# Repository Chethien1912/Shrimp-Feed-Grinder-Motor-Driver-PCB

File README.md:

# Shrimp-Feed-Grinder-Motor-Driver-PCB
Board dùng vi điều khiển STM32F0 làm trung tâm điều khiển.

STM32 xử lý các tín hiệu vào/ra, điều khiển PWM, relay, MOSFET công suất và LED 7 đoạn.

Phần driver sử dụng MOSFET công suất IRF540N để điều khiển thắng điện từ DC.

Tín hiệu điều khiển MOSFET được cách ly bằng opto PC817, giúp bảo vệ vi điều khiển khỏi nhiễu và xung áp từ tải công suất.

Mạch có diode và zener bảo vệ MOSFET khi đóng/ngắt cuộn thắng điện từ.

Board điều khiển động cơ 220VAC công suất 0.5HP thông qua relay và mạch công suất.

Khối relay dùng để điều khiển các trạng thái chạy, dừng, thắng và chuyển mạch động cơ.

Mạch khởi động mềm sử dụng nguyên lý TRIAC - DIAC, giúp giảm dòng khởi động ban đầu cho động cơ.

Điều khiển tốc độ hoặc mức công suất bằng tín hiệu PWM từ vi điều khiển.

Hiển thị trạng thái hoạt động bằng LED 7 đoạn 4 digit.

LED 7 đoạn được điều khiển qua IC TM1637, chỉ cần hai chân giao tiếp CLK và DIO.

Khối nguồn tạo các mức điện áp cần thiết như 12V, 3.3V và 55VDC.

Nguồn 3.3V cấp cho STM32 và IC hiển thị.

Nguồn 12V cấp cho relay và mạch điều khiển phụ.

Nguồn 55VDC dùng cho phần thắng điện từ.

Tổng thể board tập trung vào điều khiển phần cứng cho động cơ, gồm điều khiển PWM, thắng điện từ, khởi động mềm và hiển thị trạng thái.

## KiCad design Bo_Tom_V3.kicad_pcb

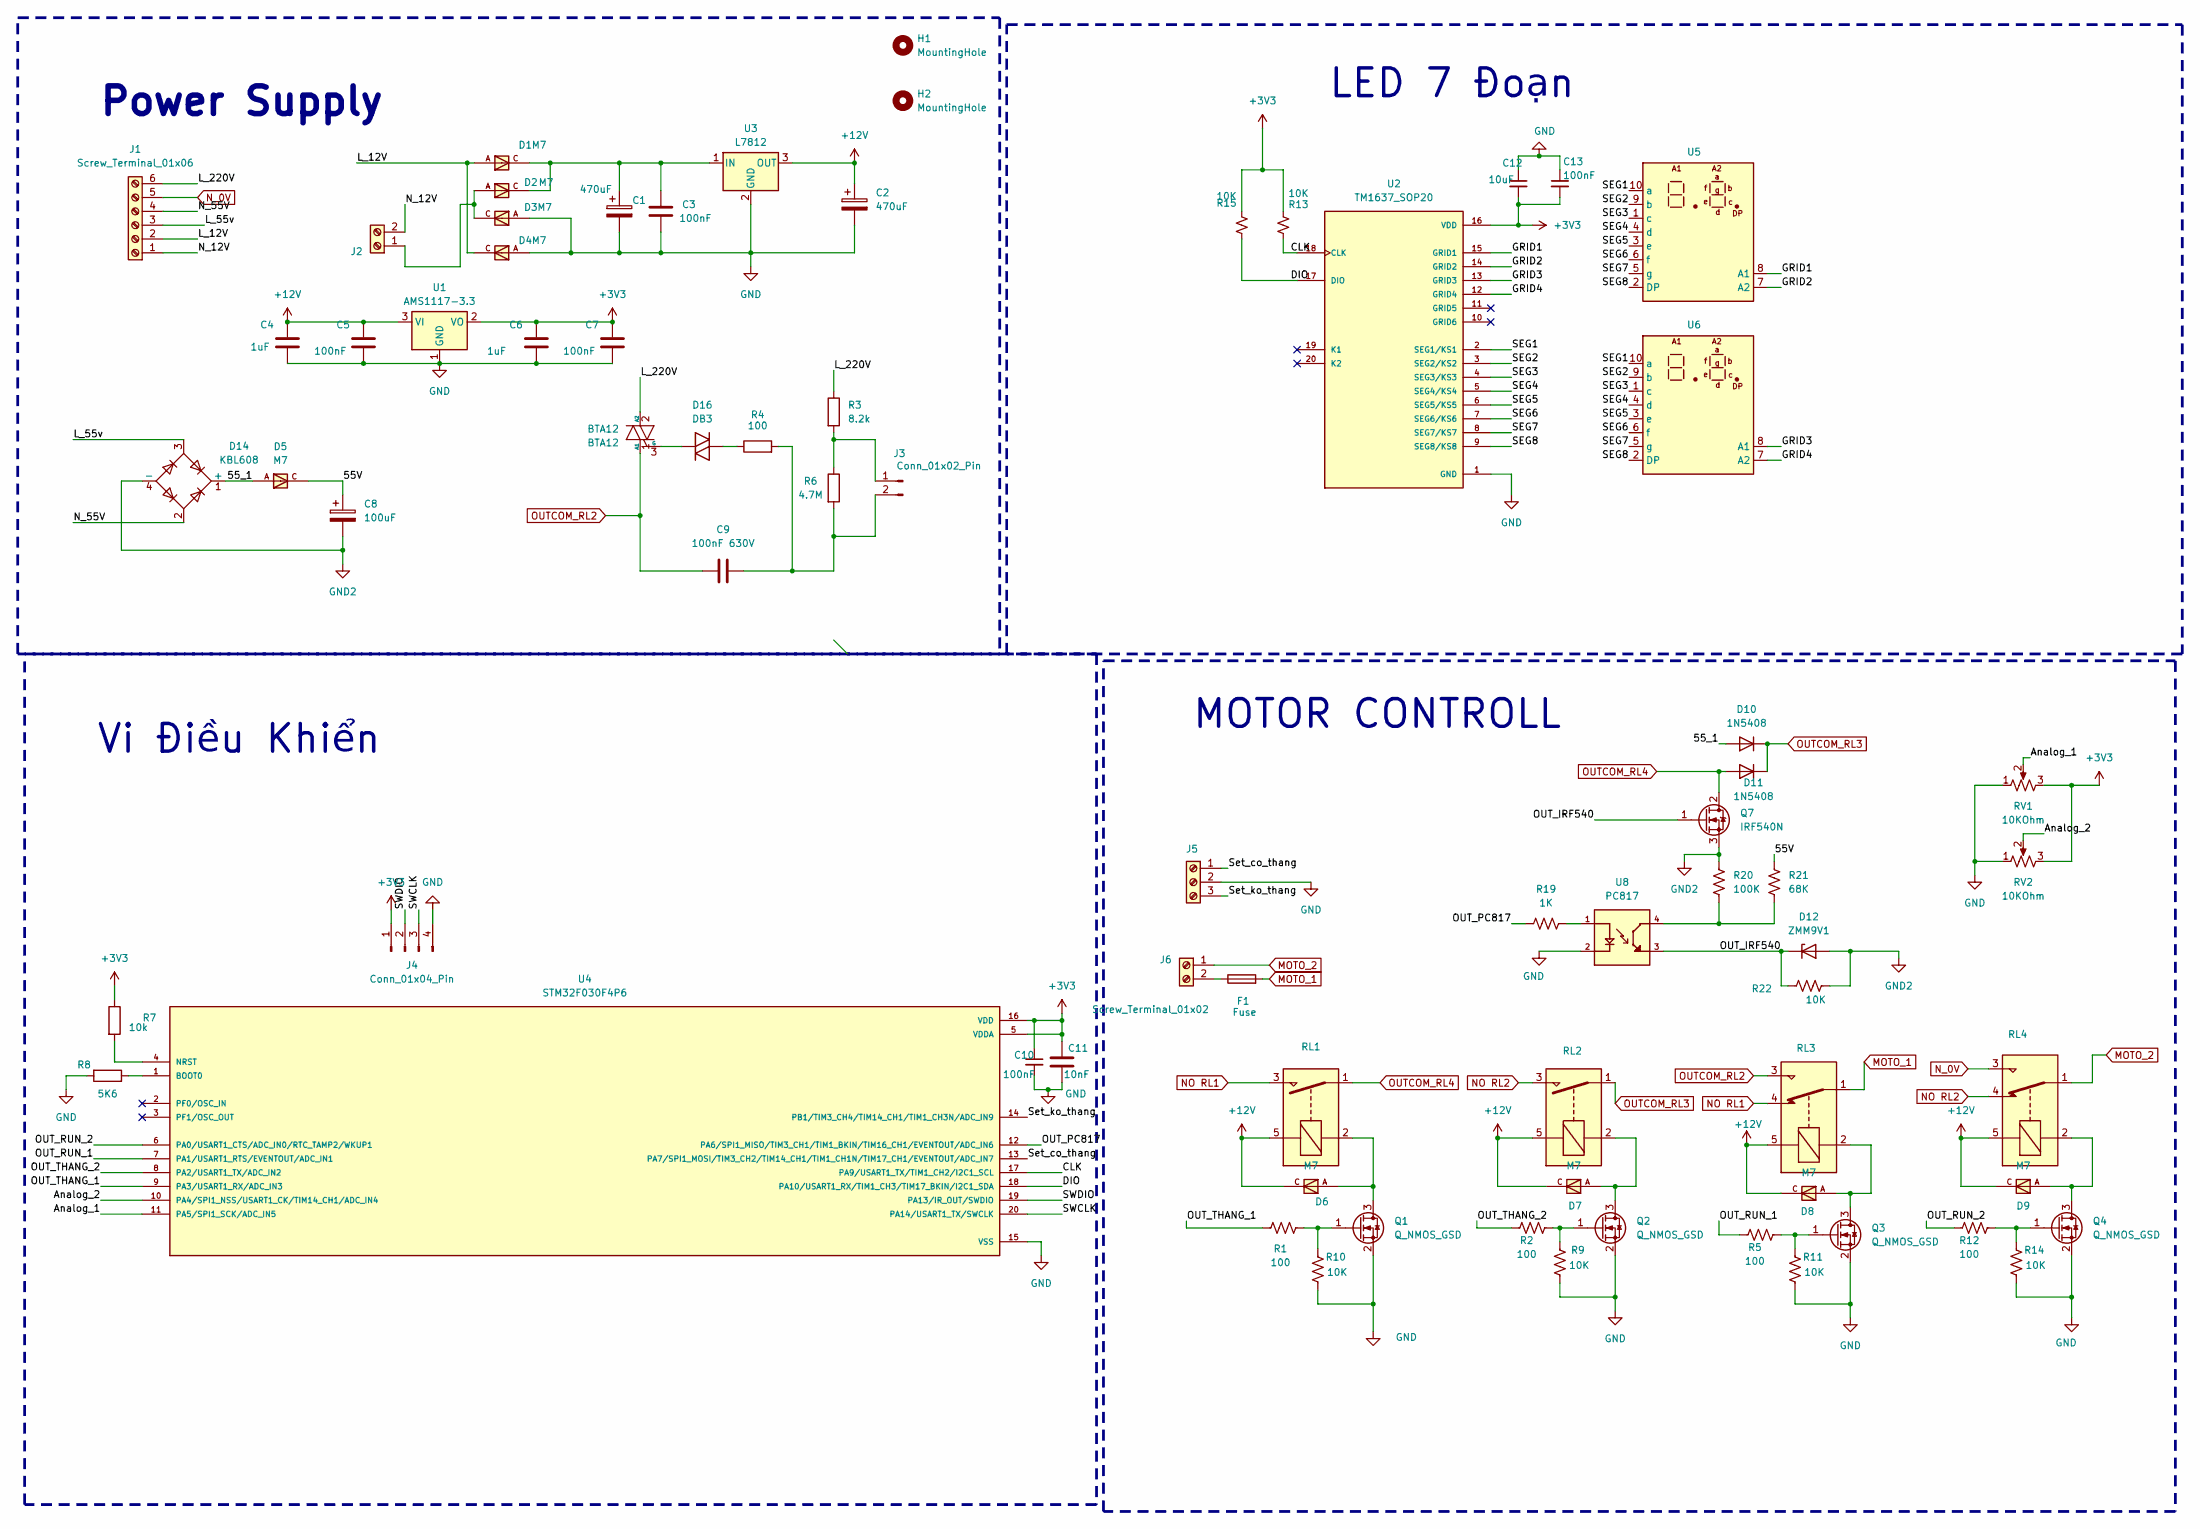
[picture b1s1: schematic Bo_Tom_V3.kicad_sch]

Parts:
BTA12: BTA12; TO-220-3_Vertical
C1, C2: 470uF; C_Radial_D8.0mm_H11.5mm_P3.50mm
C3, C5, C7, C13: 100nF; C_0603_1608Metric
C4, C6: 1uF; C_0603_1608Metric
C8: 100uF; C_Radial_D10.0mm_H16.0mm_P5.00mm
C9: 100nF 630V; C_Rect_L11.5mm_W4.5mm_P10.00mm_MKT
C10: 100nF; C_0603
C11: 10nF; C_0603_1608Metric
C12: 10uF; C_0603_1608Metric
D1, D2, D3, D4, D5, D6, D7, D8, D9: M7; DIOM505270X240; MPN M7
D10, D11: 1N5408; D_DO-201AD_P15.24mm_Horizontal
D12: ZMM9V1; diode_ZMM
D14: KBL608; KLB608
D16: DB3; D_DO-35_SOD27_P7.62mm_Horizontal
F1: Fuse; Fuse_Bourns_MF-RG300
H1, H2: MountingHole; Hole_3mm
J1: Screw_Terminal_01x06; TE_826576-6_1x06_P3.96mm_Vertical
J2, J6: Screw_Terminal_01x02; TE_826576-2_1x02_P3.96mm_Vertical
J3: Conn_01x02_Pin; Conn-Vert-THT-2P-2.54mm-S2B_XH_SM4_TB
J4: Conn_01x04_Pin; PinHeader_1x04_P2.54mm_Vertical
J5: Screw_Terminal_01x03; Conn-Vert-THT-3P-2.54mm-S3B_XH_SM4_TB
Q1, Q2, Q3, Q4: Q_NMOS_GSD; SOT-23
Q7: IRF540N; TO-220-3_Vertical
R1, R2, R5, R12: 100; R_0603_1608Metric
R3: 8.2k; R_0603
R4: 100; R_0603
R6: 4.7M; R_0805
R7: 10k; R_0603_1608Metric
R8: 5K6; R_0603_1608Metric
R9, R10, R11, R13, R14, R15, R22: 10K; R_0603_1608Metric
R19: 1K; R_0603_1608Metric
R20: 100K; R_0603_1608Metric
R21: 68K; R_0603_1608Metric
RL1, RL2: SANYOU_SRD_Form_A; Relay_SPST_SANYOU_SRD_Series_Form_A
RL3, RL4: SANYOU_SRD_Form_C; Relay_SPDT_SANYOU_SRD_Series_Form_C
RV1, RV2: 10KOhm; VR_WH148-3P-103
U1: AMS1117-3.3; SOT-223-3_TabPin2
U2: TM1637_SOP20; SOIC127P1035X255-20N; PARTREV V2.6
U3: L7812; TO-252-2
U4: STM32F030F4P6; SOP65P640X120-20N
U5, U6: Led 7 segment 2 digit
U8: PC817; SOIC254P975X460-4N

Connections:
+3V3: C6.1, C7.1, C10.1, C11.1, C12.2, C13.2, J4.1, R7.1, R13.2, R15.2, RV1.3, RV2.3, U1.2 (VO), U2.16 (VDD), U4.5 (VDDA), U4.16 (VDD)
+12V: C2.1, C4.1, C5.1, D6.C, D7.C, D8.C, D9.C, RL1.5, RL2.5, RL3.5, RL4.5, U1.3 (VI), U3.3 (OUT)
/55V: C8.1, D5.C, R21.2
/55_1: D5.A, D10.2 (A), D14.1 (+)
/Analog_1: RV1.2, U4.11 (PA5/SPI1_SCK/ADC_IN5)
/Analog_2: RV2.2, U4.10 (PA4/SPI1_NSS/USART1_CK/TIM14_CH1/ADC_IN4)
/CLK: R13.1, U2.18 (CLK), U4.17 (PA9/USART1_TX/TIM1_CH2/I2C1_SCL)
/DIO: R15.1, U2.17 (DIO), U4.18 (PA10/USART1_RX/TIM1_CH3/TIM17_BKIN/I2C1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)
/GRID1: U2.15 (GRID1), U5.8 (A1)
/GRID2: U2.14 (GRID2), U5.7 (A2)
/GRID3: U2.13 (GRID3), U6.8 (A1)
/GRID4: U2.12 (GRID4), U6.7 (A2)
/L_12V: D1.A, D4.C, J1.2
/L_55v: D14.3, J1.3
/L_220V: BTA12.2 (A2), J1.6, R3.1
/N_12V: J1.1, J2.2
/N_55V: D14.2, J1.4
/OUT_IRF540: D12.1 (K), Q7.1 (G), R22.2, U8.3
/OUT_PC817: R19.2, U4.12 (PA6/SPI1_MISO/TIM3_CH1/TIM1_BKIN/TIM16_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)
/OUT_RUN_1: R5.1, U4.7 (PA1/USART1_RTS/EVENTOUT/ADC_IN1)
/OUT_RUN_2: R12.1, U4.6 (PA0/USART1_CTS/ADC_IN0/RTC_TAMP2/WKUP1)
/OUT_THANG_1: R1.1, U4.9 (PA3/USART1_RX/ADC_IN3)
/OUT_THANG_2: R2.1, U4.8 (PA2/USART1_TX/ADC_IN2)
/SEG1: U2.2 (SEG1/KS1), U5.10 (a), U6.10 (a)
/SEG2: U2.3 (SEG2/KS2), U5.9 (b), U6.9 (b)
/SEG3: U2.4 (SEG3/KS3), U5.1 (c), U6.1 (c)
/SEG4: U2.5 (SEG4/KS4), U5.4 (d), U6.4 (d)
/SEG5: U2.6 (SEG5/KS5), U5.3 (e), U6.3 (e)
/SEG6: U2.7 (SEG6/KS6), U5.6 (f), U6.6 (f)
/SEG7: U2.8 (SEG7/KS7), U5.5 (g), U6.5 (g)
/SEG8: U2.9 (SEG8/KS8), U5.2 (DP), U6.2 (DP)
/SWCLK: J4.3, U4.20 (PA14/USART1_TX/SWCLK)
/SWDIO: J4.2, U4.19 (PA13/IR_OUT/SWDIO)
/Set_co_thang: J5.1, U4.13 (PA7/SPI1_MOSI/TIM3_CH2/TIM14_CH1/TIM1_C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)
/Set_ko_thang: J5.3, U4.14 (PB1/TIM3_CH4/TIM14_CH1/TIM1_CH3N/ADC_IN9)
GND: C1.2, C2.2, C3.2, C4.2, C5.2, C6.2, C7.2, C10.2, C11.2, C12.1, C13.1, D3.A, D4.A, J4.4, J5.2, Q1.2 (S), Q2.2 (S), Q3.2 (S), Q4.2 (S), R8.2, R9.1, R10.1, R11.1, R14.1, RV1.1, RV2.1, U1.1 (GND), U2.1 (GND), U3.2 (GND), U4.15 (VSS), U8.2
GND2: C8.2, D12.2 (A), D14.4 (-), Q7.3 (S), R20.2, R22.1
MOTO_1: F1.2, RL3.1
MOTO_2: J6.1, RL4.1
NO RL1: RL1.3, RL3.4
NO RL2: RL2.3, RL4.4
N_0V: J1.5, RL4.3
unnamed: BTA12.3 (G), D16.1 (K)
unnamed: D16.2 (A), R4.1
unnamed: D2.A, D3.C, J2.1
unnamed: J3.1, R3.2, R6.1
unnamed: C9.2, J3.2, R4.2, R6.2
unnamed: F1.1, J6.2
unnamed: D6.A, Q1.3 (D), RL1.2
unnamed: Q1.1 (G), R1.2, R10.2
unnamed: D7.A, Q2.3 (D), RL2.2
unnamed: Q2.1 (G), R2.2, R9.2
unnamed: D8.A, Q3.3 (D), RL3.2
unnamed: Q3.1 (G), R5.2, R11.2
unnamed: D9.A, Q4.3 (D), RL4.2
unnamed: Q4.1 (G), R12.2, R14.2
unnamed: R19.1, U8.1
unnamed: R20.1, R21.1, U8.4
unnamed: C1.1, C3.1, D1.C, D2.C, U3.1 (IN)
unnamed: R8.1, U4.1 (BOOT0)
unnamed: R7.2, U4.4 (NRST)
OUTCOM_RL2: BTA12.1 (A1), C9.1, RL3.3
OUTCOM_RL3: D10.1 (K), D11.1 (K), RL2.1
OUTCOM_RL4: D11.2 (A), Q7.2 (D), RL1.1

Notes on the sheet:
LED 7 Đoạn
MOTOR CONTROLL
Power Supply
Vi Điều Khiển

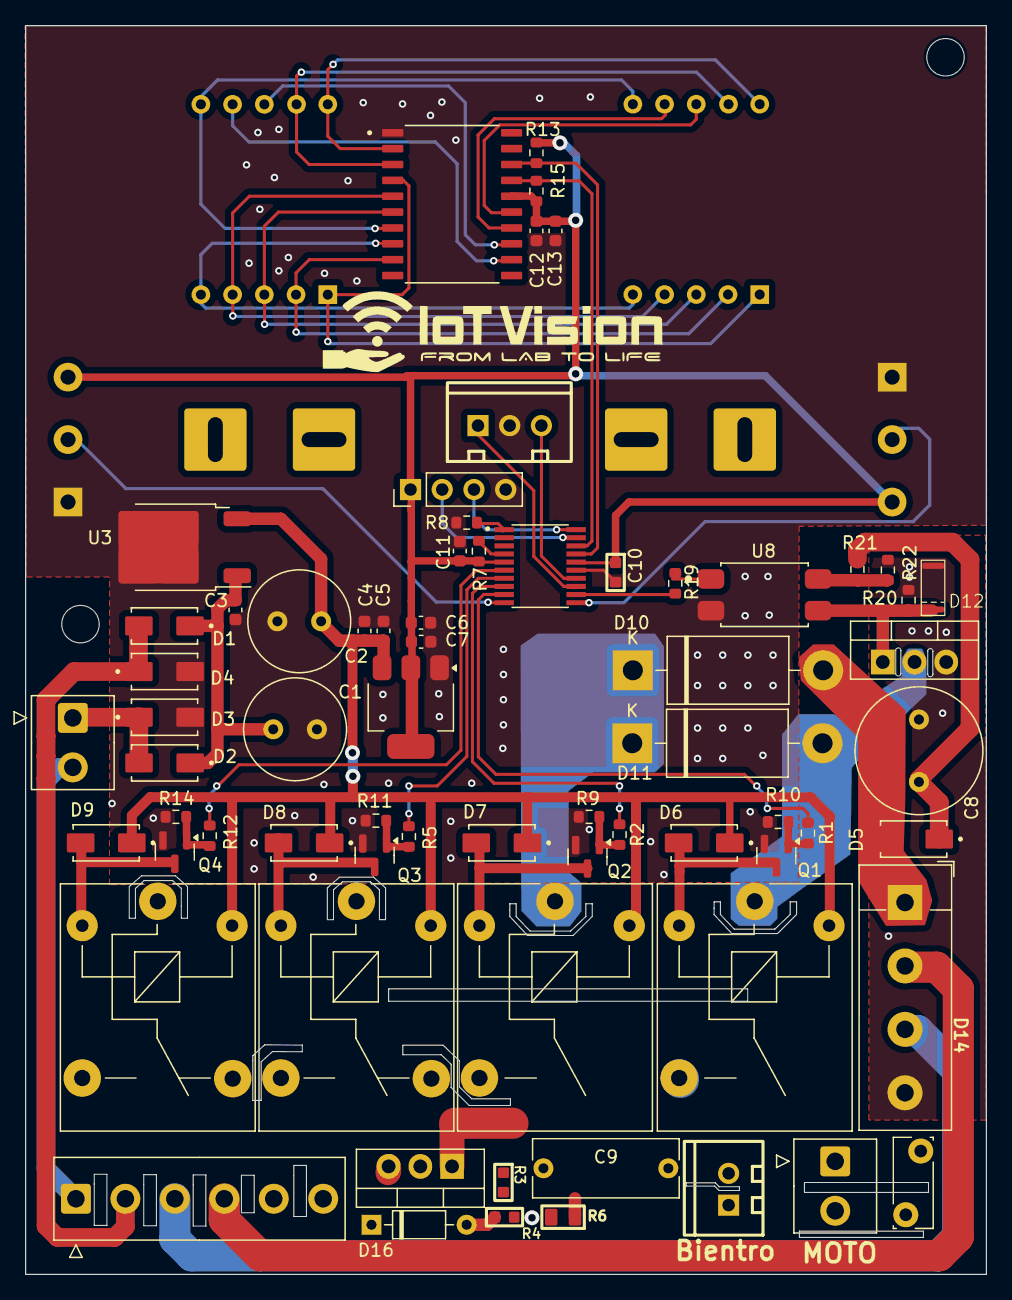
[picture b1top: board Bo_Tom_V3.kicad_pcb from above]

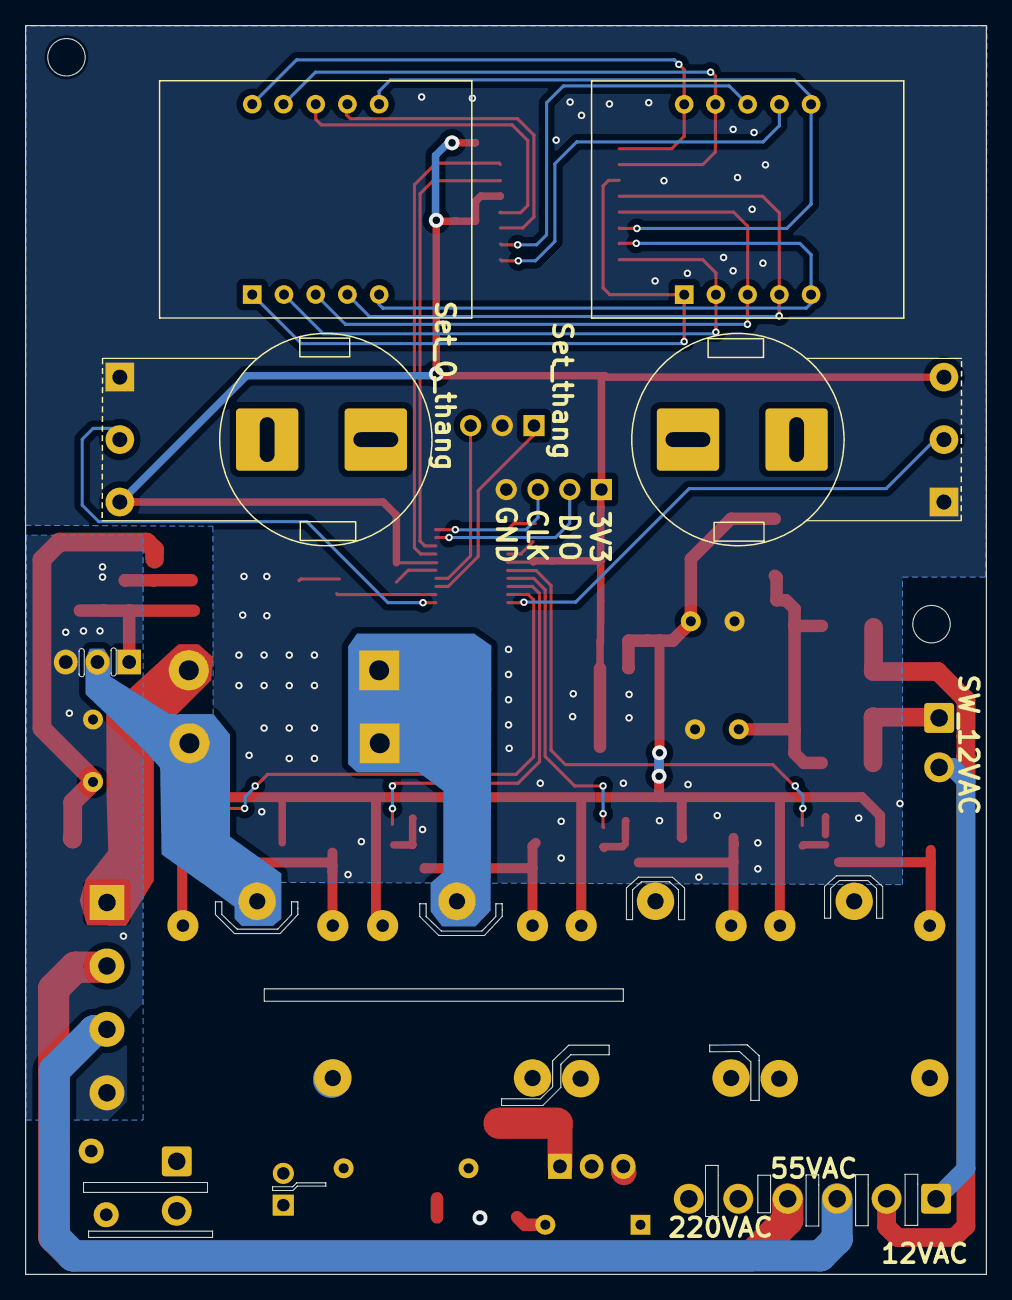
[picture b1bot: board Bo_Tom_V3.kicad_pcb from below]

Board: 2 copper layers, 76.9 x 100.0 mm, 74 parts (4 on the bottom side), 64 nets.

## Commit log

2026-05-18 Add PCB
2026-05-18 Update Project
